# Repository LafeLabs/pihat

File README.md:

# pihat
Generic Pi Hat for All the Things

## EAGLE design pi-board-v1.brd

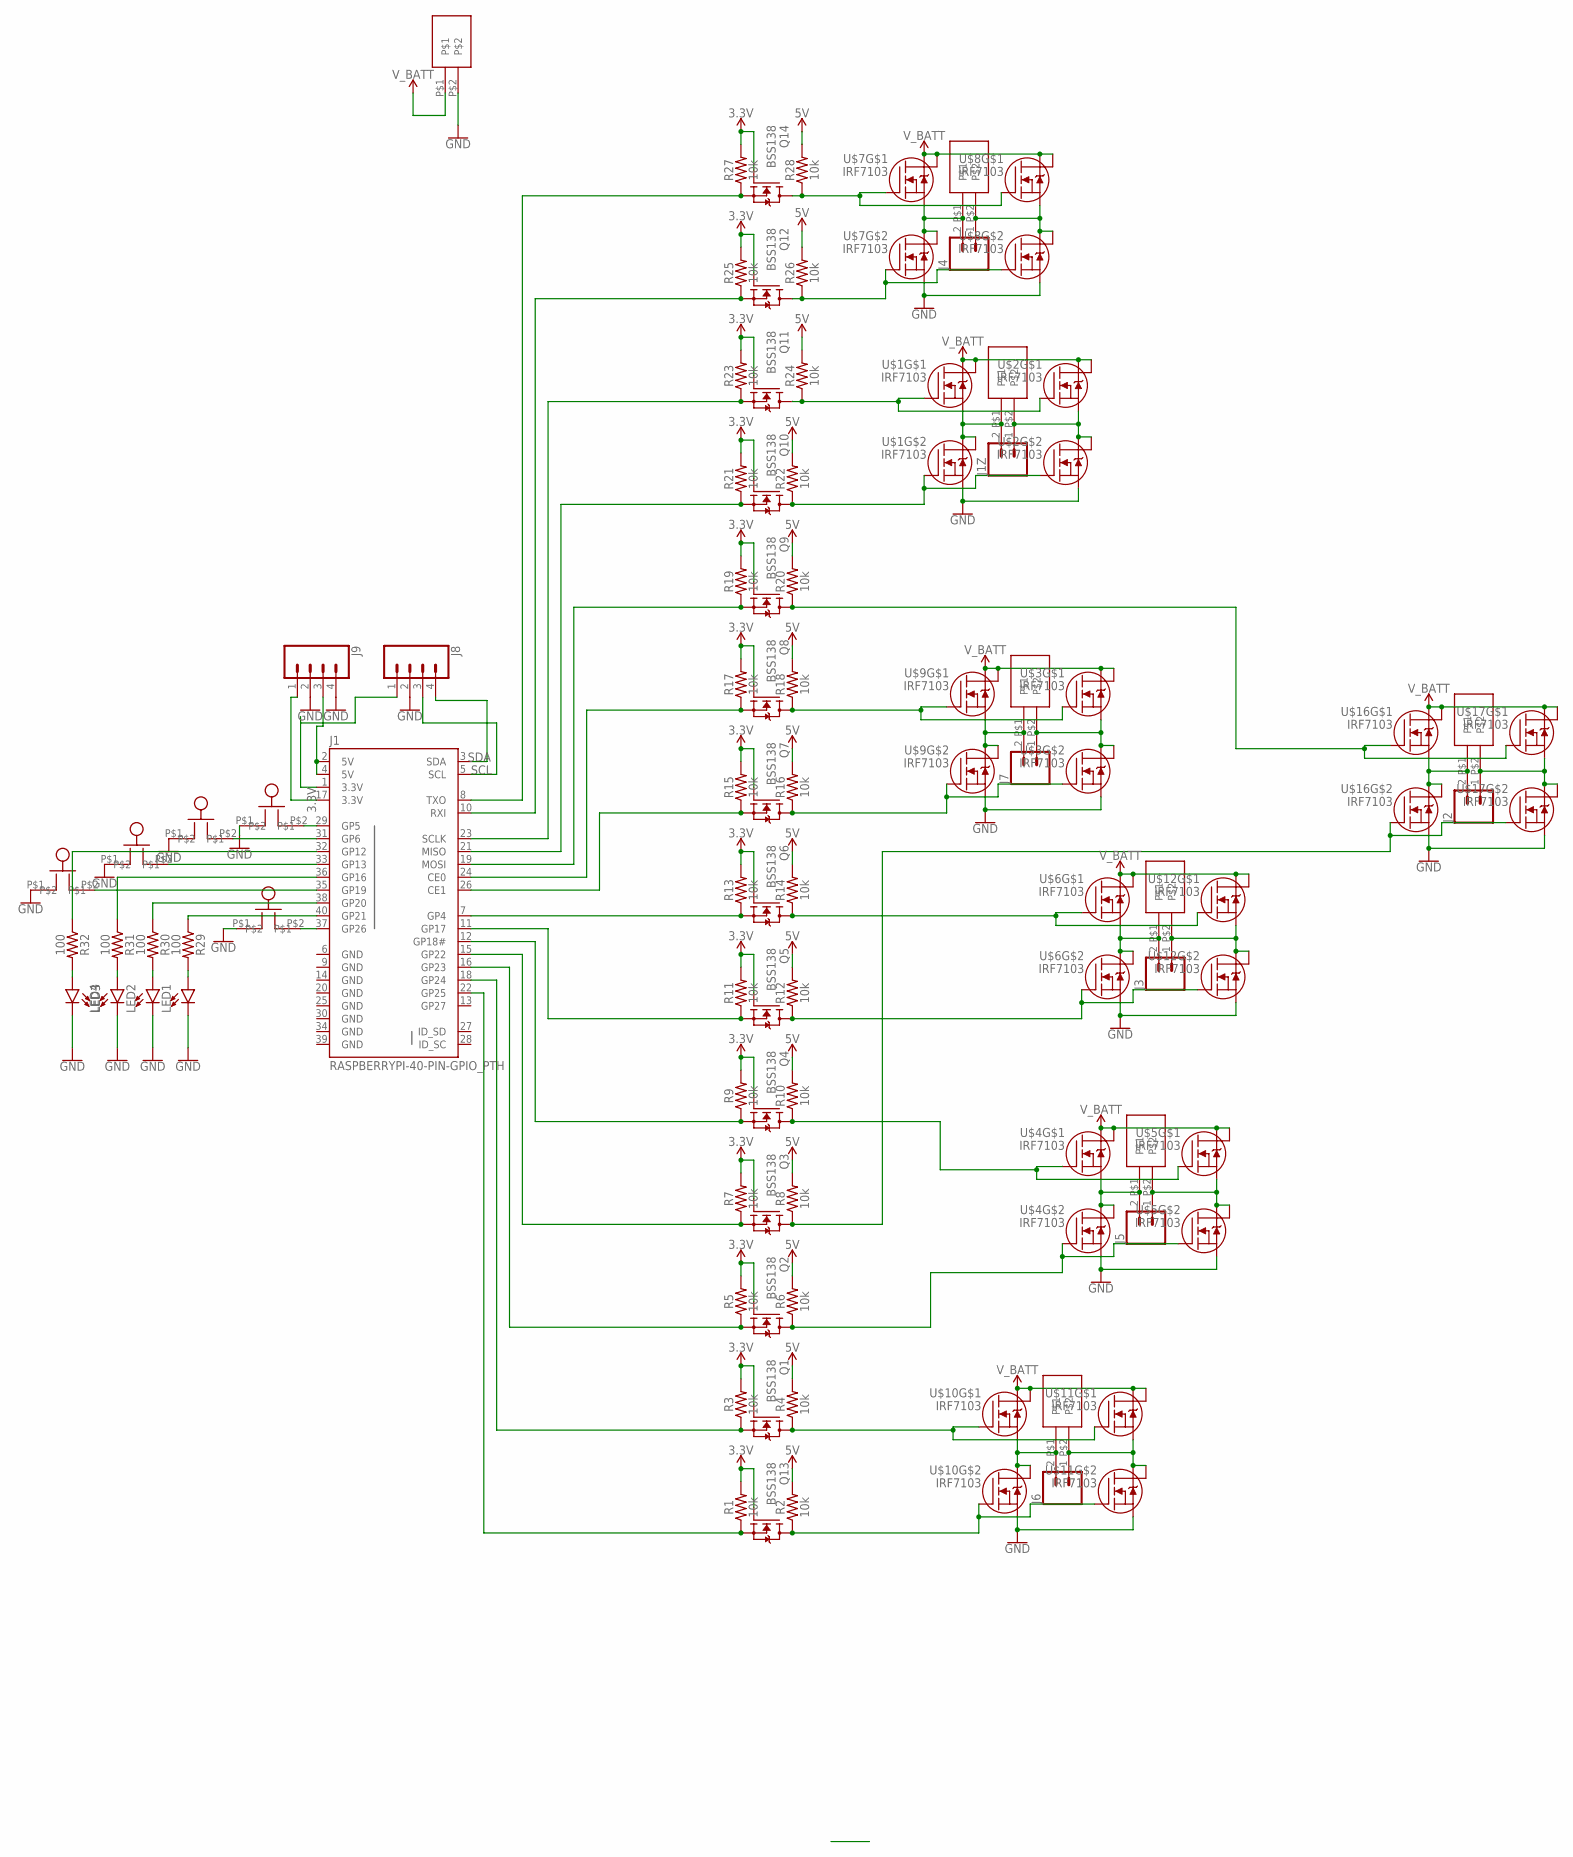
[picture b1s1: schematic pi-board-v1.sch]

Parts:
B1, B2, B3, B4, B5: BUTTON
J1: RASPBERRYPI-40-PIN-GPIO_PTH; 2X20_SHROUDED
J1Z, J2, J3, J4, J5, J6, J7: CONN_02; 1X02
J8, J9: CONN_04; 1X04
LED1, LED2, LED3, LED4: LED-3MM-NO_SILK; LED_3MM-NS
Q1, Q2, Q3, Q4, Q5, Q6, Q7, Q8, Q9, Q10, Q11, Q12, Q13, Q14: BSS138; SOT23
R1, R2, R3, R4, R5, R6, R7, R8, R9, R10, R11, R12, R13, R14, R15, R16, R17, R18, R19, R20, R21, R22, R23, R24, R25, R26, R27, R28: 10k; 0603
R29, R30, R31, R32: 100; 0603
U$1, U$2, U$3, U$4, U$5, U$6, U$7, U$8, U$9, U$10, U$11, U$12, U$16, U$17: IRF7103; SO8-2
U$22: SPRING-TERMINAL
X1, X2, X3, X4, X5, X6, X7: SPRING-TERMINAL

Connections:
3.3V: J1.1 (3.3V), J1.17 (3.3V), J8.1, J9.1, Q1.1 (G), Q2.1 (G), Q3.1 (G), Q4.1 (G), Q5.1 (G), Q6.1 (G), Q7.1 (G), Q8.1 (G), Q9.1 (G), Q10.1 (G), Q11.1 (G), Q12.1 (G), Q13.1 (G), Q14.1 (G), R1.2, R3.2, R5.2, R7.2, R9.2, R11.2, R13.2, R15.2, R17.2, R19.2, R21.2, R23.2, R25.2, R27.2
5V: J1.2 (5V), J1.4 (5V), J9.3, R2.2, R4.2, R6.2, R8.2, R10.2, R12.2, R14.2, R16.2, R18.2, R20.2, R22.2, R24.2, R26.2, R28.2
GND: B1.P$1, B2.P$1, B3.P$1, B4.P$1, B5.P$1, J1.6 (GND), J1.9 (GND), J1.14 (GND), J1.20 (GND), J1.25 (GND), J1.30 (GND), J1.34 (GND), J1.39 (GND), J8.2, J9.2, J9.4, LED1.K (C), LED2.K (C), LED3.K (C), LED4.K (C), U$1.3 (S), U$2.3 (S), U$3.3 (S), U$4.3 (S), U$5.3 (S), U$6.3 (S), U$7.3 (S), U$8.3 (S), U$9.3 (S), U$10.3 (S), U$11.3 (S), U$12.3 (S), U$16.3 (S), U$17.3 (S), U$22.P$2
unnamed: J1.22 (GP25), Q13.2 (S), R1.1
unnamed: Q11.3 (D), R24.1, U$1.2 (G), U$2.2 (G)
unnamed: J1.18 (GP24), Q1.2 (S), R3.1
unnamed: J1Z.2, U$1.1 (S), U$1.5 (D), U$1.6 (D), X1.P$1
unnamed: J1.16 (GP23), Q2.2 (S), R5.1
unnamed: J1Z.1, U$2.1 (S), U$2.5 (D), U$2.6 (D), X1.P$2
unnamed: J1.15 (GP22), Q3.2 (S), R7.1
unnamed: Q3.3 (D), R8.1, U$16.4 (G), U$17.4 (G)
unnamed: Q8.3 (D), R18.1, U$3.2 (G), U$9.2 (G)
unnamed: Q12.3 (D), R26.1, U$7.4 (G), U$8.4 (G)
unnamed: J1.11 (GP17), Q5.2 (S), R11.1
unnamed: Q5.3 (D), R12.1, U$6.4 (G), U$12.4 (G)
unnamed: J1.7 (GP4), Q6.2 (S), R13.1
unnamed: Q10.3 (D), R22.1, U$1.4 (G), U$2.4 (G)
unnamed: J1.26 (CE1), Q7.2 (S), R15.1
unnamed: B5.P$2, J1.37 (GP26)
unnamed: J1.24 (CE0), Q8.2 (S), R17.1
unnamed: J7.2, U$9.1 (S), U$9.5 (D), U$9.6 (D), X7.P$1
unnamed: J1.19 (MOSI), Q9.2 (S), R19.1
unnamed: Q9.3 (D), R20.1, U$16.2 (G), U$17.2 (G)
unnamed: J1.21 (MISO), Q10.2 (S), R21.1
unnamed: J5.2, U$4.1 (S), U$4.5 (D), U$4.6 (D), X5.P$1
unnamed: J1.23 (SCLK), Q11.2 (S), R23.1
unnamed: J7.1, U$3.1 (S), U$3.5 (D), U$3.6 (D), X7.P$2
unnamed: J1.10 (RXI), Q12.2 (S), R25.1
unnamed: J5.1, U$5.1 (S), U$5.5 (D), U$5.6 (D), X5.P$2
unnamed: J1.8 (TXO), Q14.2 (S), R27.1
unnamed: Q14.3 (D), R28.1, U$7.2 (G), U$8.2 (G)
unnamed: Q7.3 (D), R16.1, U$3.4 (G), U$9.4 (G)
unnamed: B4.P$2, J1.35 (GP19)
unnamed: B3.P$2, J1.33 (GP13)
unnamed: J1.12 (GP18#), Q4.2 (S), R9.1
unnamed: Q6.3 (D), R14.1, U$6.2 (G), U$12.2 (G)
unnamed: Q4.3 (D), R10.1, U$4.2 (G), U$5.2 (G)
unnamed: Q13.3 (D), R2.1, U$10.4 (G), U$11.4 (G)
unnamed: Q2.3 (D), R6.1, U$4.4 (G), U$5.4 (G)
unnamed: J6.2, U$10.1 (S), U$10.5 (D), U$10.6 (D), X6.P$1
unnamed: J4.2, U$7.1 (S), U$7.5 (D), U$7.6 (D), X4.P$1
unnamed: J4.1, U$8.1 (S), U$8.5 (D), U$8.6 (D), X4.P$2
unnamed: J6.1, U$11.1 (S), U$11.5 (D), U$11.6 (D), X6.P$2
unnamed: J2.2, U$16.1 (S), U$16.5 (D), U$16.6 (D), X2.P$1
unnamed: J2.1, U$17.1 (S), U$17.5 (D), U$17.6 (D), X2.P$2
unnamed: B1.P$2, J1.29 (GP5)
unnamed: B2.P$2, J1.31 (GP6)
unnamed: Q1.3 (D), R4.1, U$10.2 (G), U$11.2 (G)
unnamed: J3.2, U$6.1 (S), U$6.5 (D), U$6.6 (D), X3.P$1
unnamed: J3.1, U$12.1 (S), U$12.5 (D), U$12.6 (D), X3.P$2
unnamed: LED4.A, R32.2
unnamed: LED3.A, R31.2
unnamed: LED2.A, R30.2
unnamed: LED1.A, R29.2
unnamed: J1.40 (GP21), R29.1
unnamed: J1.38 (GP20), R30.1
unnamed: J1.36 (GP16), R31.1
unnamed: J1.32 (GP12), R32.1
SCL: J1.5 (SCL), J8.3
SDA: J1.3 (SDA), J8.4
V_BATT: U$1.7 (D), U$1.8 (D), U$2.7 (D), U$2.8 (D), U$3.7 (D), U$3.8 (D), U$4.7 (D), U$4.8 (D), U$5.7 (D), U$5.8 (D), U$6.7 (D), U$6.8 (D), U$7.7 (D), U$7.8 (D), U$8.7 (D), U$8.8 (D), U$9.7 (D), U$9.8 (D), U$10.7 (D), U$10.8 (D), U$11.7 (D), U$11.8 (D), U$12.7 (D), U$12.8 (D), U$16.7 (D), U$16.8 (D), U$17.7 (D), U$17.8 (D), U$22.P$1

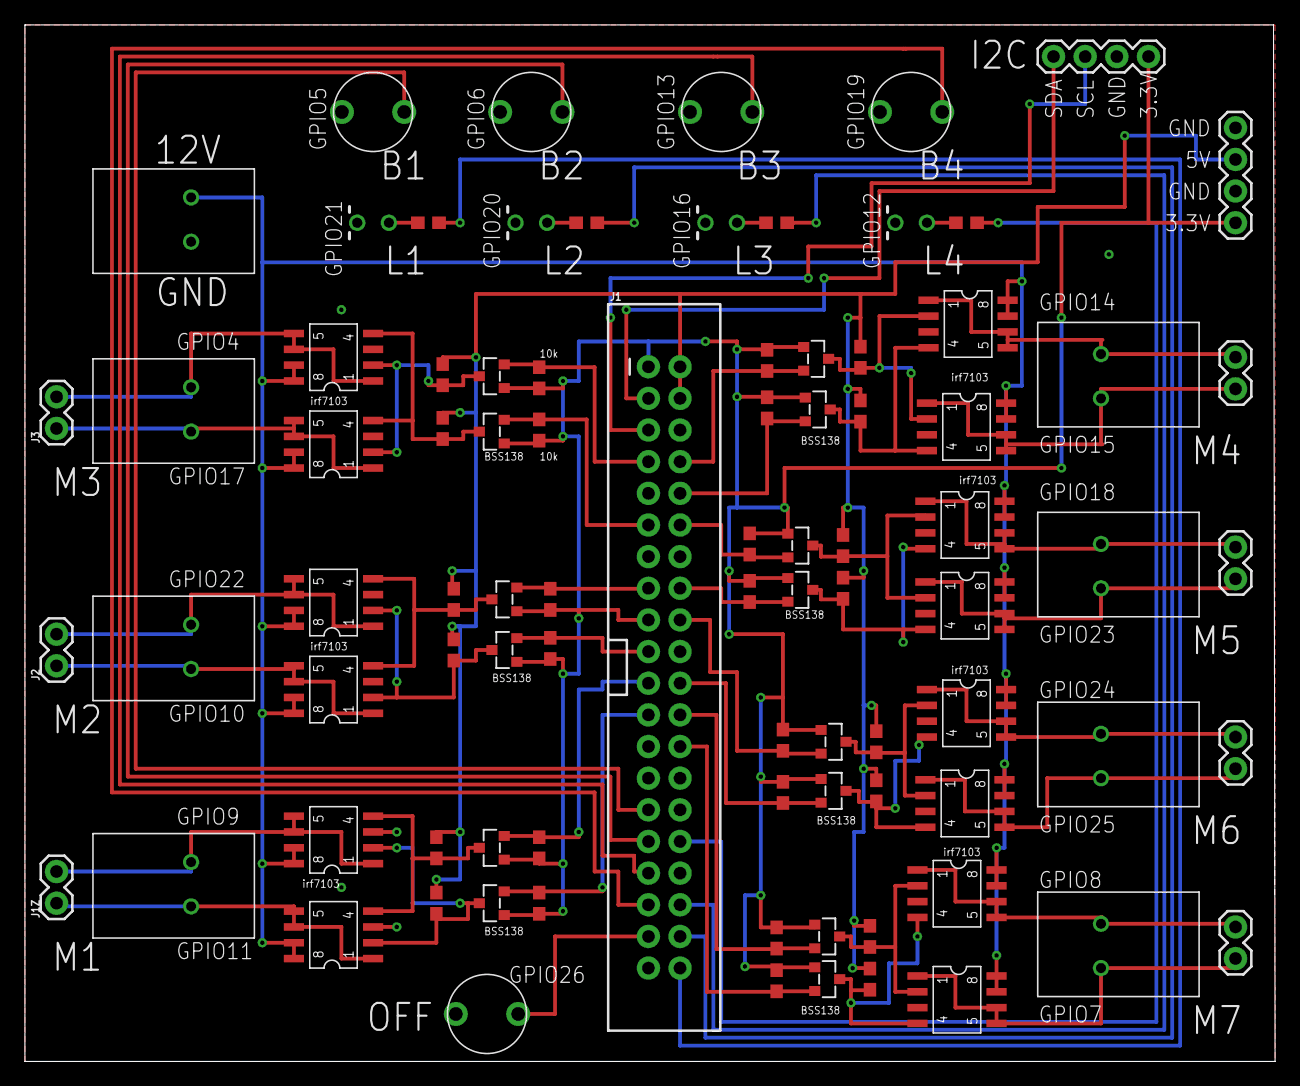
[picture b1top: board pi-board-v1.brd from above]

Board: 2 copper layers, 100.3 x 83.2 mm, 87 parts (0 on the bottom side), 61 nets.

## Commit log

2020-04-10 moved eagle files to pihat git hub repo from local directory

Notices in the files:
parts and their libraries:
SparkFun-Connectors: Licensing: Creative Commons ShareAlike 4.0 International - https://creativecommons.org/licenses/by-sa/4.0
irf-7103: Copyright & License
This library is licensed under the General Public License, Version 2.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
